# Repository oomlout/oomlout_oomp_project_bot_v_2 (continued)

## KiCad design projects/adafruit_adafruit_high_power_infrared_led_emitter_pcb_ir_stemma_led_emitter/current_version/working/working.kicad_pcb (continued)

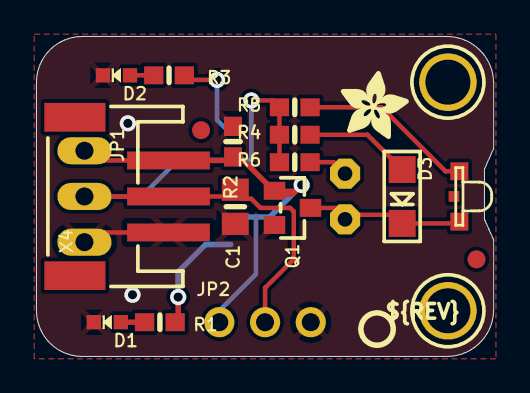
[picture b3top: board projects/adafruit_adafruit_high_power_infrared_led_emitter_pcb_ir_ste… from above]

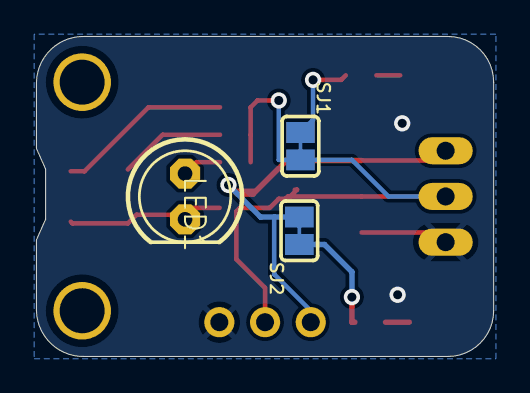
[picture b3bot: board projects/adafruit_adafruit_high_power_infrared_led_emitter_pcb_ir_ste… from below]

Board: 16 copper layers, 25.4 x 17.8 mm, 39 parts (14 on the bottom side), 11 nets.

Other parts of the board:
PLABEL0: PLABEL0
PLABEL00: PLABEL00
PLABEL1: PLABEL1
PLABEL2: PLABEL2
PLABEL3: PLABEL3
PLABEL4: PLABEL4
PLABEL5: PLABEL5
PLABEL6: PLABEL6
PLABEL7: PLABEL7
PLABEL8: PLABEL8
PLABEL9: PLABEL9
PLABEL10: PLABEL10
PLABEL11: PLABEL11
PLABEL13: PLABEL13
PLABEL14: PLABEL14
U$5: PCBFEAT-REV-040
U$10: ADAFRUIT_3.5MM

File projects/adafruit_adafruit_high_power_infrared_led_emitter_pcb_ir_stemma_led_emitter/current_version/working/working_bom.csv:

"Id";"Designator";"Footprint";"Quantity";"Designation";"Supplier and ref";
1;"Q1";"SOT23-WIDE";1;"AO3406";;;
2;"FID3,FID2";"FIDUCIAL_1MM";2;"FIDUCIAL_1MM";;;
3;"PLABEL1";"PLABEL1";1;"";;;
4;"D3";"CHIPLED_1206";1;"1206 IR 940nm";;;
5;"PLABEL2";"PLABEL2";1;"";;;
6;"X4";"JSTPH3";1;"JST PH 3";;;
7;"R6,R4,R5";"0603-NO";3;"22";;;
8;"R1,R2";"0603-NO";2;"10K";;;
9;"D4";"LED_1206_SIDE";1;"1206 IR 940nm Side";;;
10;"PLABEL3";"PLABEL3";1;"";;;
11;"D1";"CHIPLED_0603_NOOUTLINE";1;"RED";;;
12;"C1";"0805-NO";1;"10uF";;;
13;"PLABEL0";"PLABEL0";1;"";;;
14;"U$1,U$8";"MOUNTINGHOLE_2.5_PLATED";2;"MOUNTINGHOLE2.5";;;
15;"U$5";"PCBFEAT-REV-040";1;"";;;
16;"D2";"CHIPLED_0603_NOOUTLINE";1;"GREEN";;;
17;"JP1";"1X03_OVAL";1;"0.1" Header";;;
18;"R3";"0603-NO";1;"33K";;;
19;"JP2";"1X03_ROUND";1;"0.1" Header";;;
20;"U$10";"ADAFRUIT_3.5MM";1;"";;;
21;"PLABEL11";"PLABEL11";1;"";;;
22;"PLABEL13";"PLABEL13";1;"";;;
23;"SJ1,SJ2";"SOLDERJUMPER_CLOSEDWIRE";2;"";;;
24;"PLABEL6";"PLABEL6";1;"";;;
25;"PLABEL9";"PLABEL9";1;"";;;
26;"LED1";"LED5MM";1;"5mm";;;
27;"PLABEL7";"PLABEL7";1;"";;;
28;"PLABEL5";"PLABEL5";1;"";;;
29;"PLABEL4";"PLABEL4";1;"";;;
30;"PLABEL8";"PLABEL8";1;"";;;
31;"PLABEL10";"PLABEL10";1;"";;;
32;"PLABEL14";"PLABEL14";1;"";;;
33;"PLABEL00";"PLABEL00";1;"";;;

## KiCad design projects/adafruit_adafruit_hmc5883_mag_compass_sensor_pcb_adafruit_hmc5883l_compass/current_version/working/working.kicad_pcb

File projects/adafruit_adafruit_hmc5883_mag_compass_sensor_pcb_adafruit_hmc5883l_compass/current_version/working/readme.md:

# adafruit_hmc5883_mag_compass_sensor_pcb
 
## summary 
* id: adafruit_adafruit_hmc5883_mag_compass_sensor_pcb_adafruit_hmc5883l_compass
* user: adafruit
* name: adafruit_hmc5883_mag_compass_sensor_pcb
* board: adafruit_hmc5883l_compass
* repo: https://github.com/adafruit/Adafruit-HMC5883-Mag-Compass-Sensor-PCB

* src_file_repo_sch: 
* src_file_repo_sch_link: https://github.com/adafruit/Adafruit-HMC5883-Mag-Compass-Sensor-PCB/tree/master/
* full details link: https://github.com/oomlout/oomlout_oomp_project_bot_v_2/tree/main/projects/adafruit_adafruit_hmc5883_mag_compass_sensor_pcb_adafruit_hmc5883l_compass/current_version/working  

## schematic  
  
[schematic (pdf)](working_schematic.pdf) 

## pcb  

[board (pdf)](working.pdf)  

## working_bom
| Id | Designator | Footprint | Quantity | Designation | Supplier and ref |  | None | 
| --- | --- | --- | --- | --- | --- | --- | --- | 
| 1 | Q2,Q1 | SOT23-WIDE | 2 | BSS138 |  |  | [''] | 
| 2 | R4,R3 | 0805-NO | 2 | 10K |  |  | [''] | 
| 3 | C3,C5 | C0805 | 2 | 10uF |  |  | [''] | 
| 4 | U2 | SOT23-5 | 1 | MIC5225-3.3V |  |  | [''] | 
| 5 | U$12,U$10,U$11 | FIDUCIAL_1MM | 3 | FIDUCIAL |  |  | [''] | 
| 6 | U$9,U$8 | MOUNTINGHOLE_2.5_PLATED | 2 | MOUNTINGHOLE2.5 |  |  | [''] | 
| 7 | U1 | HMC5883L | 1 | HMC5883L-T |  |  | [''] | 
| 8 | R2,R1 | _0805MP | 2 | 10K |  |  | [''] | 
| 9 | C2 | 0805_10MGAP | 1 | 4.7uF |  |  | [''] | 
| 10 | C4 | C0805 | 1 | 0.22uF |  |  | [''] | 
| 11 | JP1 | 1X06_ROUND_76 | 1 |  |  |  | [''] | 
| 12 | U$7 | ADAFRUIT_5MM | 1 |  |  |  | [''] | 

## bom_schematic
| Ref | Qnty | Value | Cmp name | Footprint | Description | Vendor | DNP | 
| --- | --- | --- | --- | --- | --- | --- | --- | 
| C2 | 1 | 4.7uF | CAP_CERAMIC0805_10MGAP | working:0805_10MGAP |  |  |  | 
| C3, C5 | 2 | 10uF | C-USC0805 | working:C0805 |  |  |  | 
| C4 | 1 | 0.22uF | C-USC0805 | working:C0805 |  |  |  | 
| JP1 | 1 | HEADER-1X676MIL | HEADER-1X676MIL | working:1X06_ROUND_76 |  |  |  | 
| Q1, Q2 | 2 | BSS138 | MOSFET-NWIDE | working:SOT23-WIDE |  |  |  | 
| R1, R2 | 2 | 10K | RESISTOR_0805MP | working:_0805MP |  |  |  | 
| R3, R4 | 2 | 10K | RESISTOR0805_NOOUTLINE | working:0805-NO |  |  |  | 
| U1 | 1 | HMC5883L-T | HMC5883L | working:HMC5883L |  |  |  | 
| U2 | 1 | MIC5225-3.3V | VREG_SOT23-5 | working:SOT23-5 |  |  |  | 
| U$8, U$9 | 2 | MOUNTINGHOLE2.5 | MOUNTINGHOLE2.5 | working:MOUNTINGHOLE_2.5_PLATED |  |  |  | 
| U$10, U$11, U$12 | 3 | FIDUCIAL | FIDUCIAL | working:FIDUCIAL_1MM |  |  |  | 

## mounting_holes
| x | y | package | value | ref | size | 
| --- | --- | --- | --- | --- | --- | 
| 0.0 | 0.0 | MOUNTINGHOLE_2.5_PLATED | MOUNTINGHOLE2.5 | U$8 | m3 | 
| 13.21 | 0.0 | MOUNTINGHOLE_2.5_PLATED | MOUNTINGHOLE2.5 | U$9 | m3 |

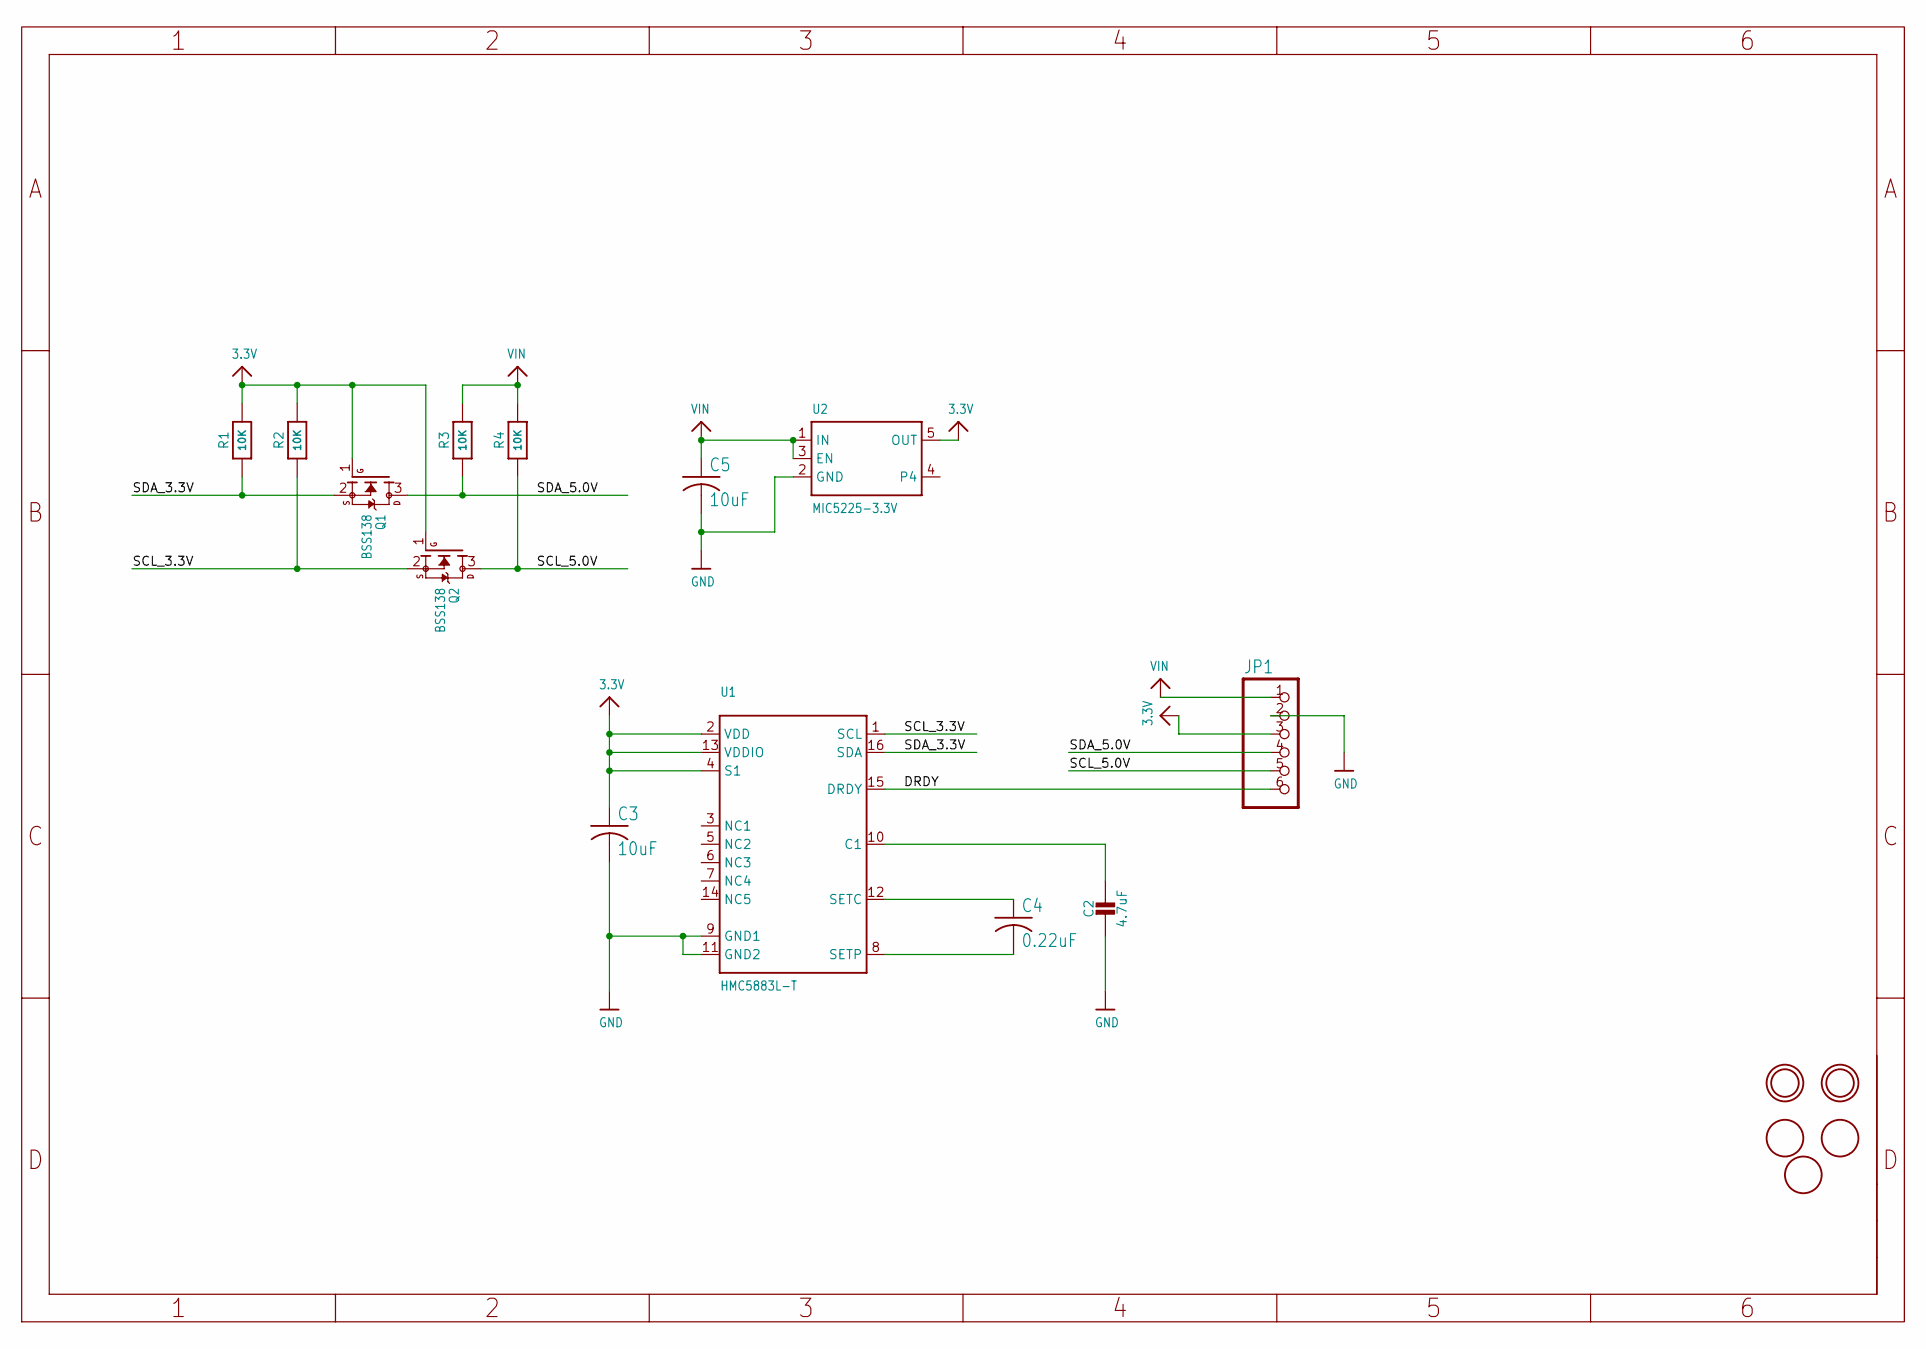
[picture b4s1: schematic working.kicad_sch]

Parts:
C2: 4.7uF; 0805_10MGAP
C3, C5: 10uF; C0805
C4: 0.22uF; C0805
JP1: HEADER-1X676MIL; 1X06_ROUND_76
Q1, Q2: BSS138; SOT23-WIDE
R1, R2: 10K; _0805MP
R3, R4: 10K; 0805-NO
U1: HMC5883L-T; HMC5883L
U2: MIC5225-3.3V; SOT23-5
U$8, U$9: MOUNTINGHOLE2.5; MOUNTINGHOLE_2.5_PLATED
U$10, U$11, U$12: FIDUCIAL; FIDUCIAL_1MM

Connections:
3.3V: C3.1, JP1.3, Q1.1 (G), Q2.1 (G), R1.2, R2.2, U1.2 (VDD), U1.4 (S1), U1.13 (VDDIO), U2.5 (OUT)
DRDY: JP1.6, U1.15 (DRDY)
GND: C2.2, C3.2, C5.2, JP1.2, U1.9 (GND1), U1.11 (GND2), U2.2 (GND)
unnamed: C4.1, U1.12 (SETC)
unnamed: C4.2, U1.8 (SETP)
unnamed: C2.1, U1.10 (C1)
SCL_3.3V: Q2.2 (S), R2.1, U1.1 (SCL)
SCL_5.0V: JP1.5, Q2.3 (D), R4.1
SDA_3.3V: Q1.2 (S), R1.1, U1.16 (SDA)
SDA_5.0V: JP1.4, Q1.3 (D), R3.1
VIN: C5.1, JP1.1, R3.2, R4.2, U2.1 (IN), U2.3 (EN)

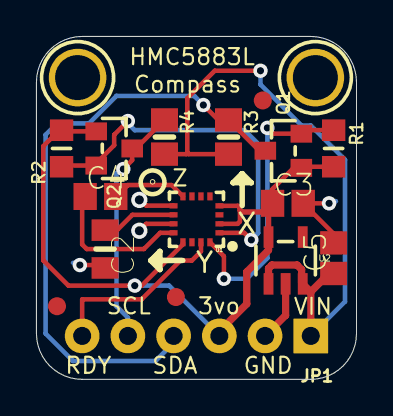
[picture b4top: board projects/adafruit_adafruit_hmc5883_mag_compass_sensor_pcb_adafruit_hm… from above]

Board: 2 copper layers, 17.8 x 19.0 mm, 19 parts (1 on the bottom side), 11 nets.

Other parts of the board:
U$7: ADAFRUIT_5MM

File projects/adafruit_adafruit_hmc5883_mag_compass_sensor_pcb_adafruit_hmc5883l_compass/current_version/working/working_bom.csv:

"Id";"Designator";"Footprint";"Quantity";"Designation";"Supplier and ref";
1;"Q2,Q1";"SOT23-WIDE";2;"BSS138";;;
2;"R4,R3";"0805-NO";2;"10K";;;
3;"C3,C5";"C0805";2;"10uF";;;
4;"U2";"SOT23-5";1;"MIC5225-3.3V";;;
5;"U$12,U$10,U$11";"FIDUCIAL_1MM";3;"FIDUCIAL";;;
6;"U$9,U$8";"MOUNTINGHOLE_2.5_PLATED";2;"MOUNTINGHOLE2.5";;;
7;"U1";"HMC5883L";1;"HMC5883L-T";;;
8;"R2,R1";"_0805MP";2;"10K";;;
9;"C2";"0805_10MGAP";1;"4.7uF";;;
10;"C4";"C0805";1;"0.22uF";;;
11;"JP1";"1X06_ROUND_76";1;"";;;
12;"U$7";"ADAFRUIT_5MM";1;"";;;

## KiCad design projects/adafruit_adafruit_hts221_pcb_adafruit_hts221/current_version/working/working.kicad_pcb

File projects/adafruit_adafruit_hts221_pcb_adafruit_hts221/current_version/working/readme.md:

# adafruit_hts221_pcb
 
## summary 
* id: adafruit_adafruit_hts221_pcb_adafruit_hts221
* user: adafruit
* name: adafruit_hts221_pcb
* board: adafruit_hts221
* repo: https://github.com/adafruit/Adafruit-HTS221-PCB

* src_file_repo_sch: 
* src_file_repo_sch_link: https://github.com/adafruit/Adafruit-HTS221-PCB/tree/master/
* full details link: https://github.com/oomlout/oomlout_oomp_project_bot_v_2/tree/main/projects/adafruit_adafruit_hts221_pcb_adafruit_hts221/current_version/working  

## schematic  
  
[schematic (pdf)](working_schematic.pdf) 

## pcb  

[board (pdf)](working.pdf)  

## working_bom
| Id | Designator | Footprint | Quantity | Designation | Supplier and ref |  | None | 
| --- | --- | --- | --- | --- | --- | --- | --- | 
| 1 | U2 | SOT23-5 | 1 | AP2112K-3.3 |  |  | [''] | 
| 2 | U$17,U$1 | MOUNTINGHOLE_2.5_PLATED | 2 | MOUNTINGHOLE2.5 |  |  | [''] | 
| 3 | @HOLE0,@HOLE1 |  | 2 |  |  |  | [''] | 
| 4 | C1 | 0603-NO | 1 | 0.1uF |  |  | [''] | 
| 5 | JP1 | 1X07_ROUND_70 | 1 |  |  |  | [''] | 
| 6 | CONN4,CONN3 | JST_SH4 | 2 | STEMMA_I2C_QT |  |  | [''] | 
| 7 | R5,R1 | 0603-NO | 2 | 10K |  |  | [''] | 
| 8 | D1 | CHIPLED_0603_NOOUTLINE | 1 | GREEN |  |  | [''] | 
| 9 | FID4,FID3 | FIDUCIAL_1MM | 2 | FIDUCIAL_1MM |  |  | [''] | 
| 10 | X1 | HLGA-6L | 1 | HTS221 |  |  | [''] | 
| 11 | C2,C3 | 0805-NO | 2 | 10uF |  |  | [''] | 
| 12 | D2 | SOD-323 | 1 | 1N4148 |  |  | [''] | 
| 13 | U$4 | ADAFRUIT_3.5MM | 1 |  |  |  | [''] | 
| 14 | R3 | RESPACK_4X0603 | 1 | 10K |  |  | [''] | 
| 15 | Q2 | SOT363 | 1 | BSS138 |  |  | [''] | 
| 16 | U$25 | PCBFEAT-REV-040 | 1 |  |  |  | [''] | 
| 17 | U$30,U$31 | STEMMAQT | 2 |  |  |  | [''] | 

## bom_schematic
| Ref | Qnty | Value | Cmp name | Footprint | Description | Vendor | DNP | 
| --- | --- | --- | --- | --- | --- | --- | --- | 
| C1 | 1 | 0.1uF | CAP_CERAMIC0603_NO | working:0603-NO |  |  |  | 
| C2, C3 | 2 | 10uF | CAP_CERAMIC0805-NOOUTLINE | working:0805-NO |  |  |  | 
| CONN3, CONN4 | 2 | STEMMA_I2C_QT | STEMMA_I2C_QT | working:JST_SH4 |  |  |  | 
| D1 | 1 | GREEN | LED0603_NOOUTLINE | working:CHIPLED_0603_NOOUTLINE |  |  |  | 
| D2 | 1 | 1N4148 | DIODESOD-323 | working:SOD-323 |  |  |  | 
| FID3, FID4 | 2 | FIDUCIAL_1MM | FIDUCIAL_1MM | working:FIDUCIAL_1MM |  |  |  | 
| JP1 | 1 | HEADER-1X770MIL | HEADER-1X770MIL | working:1X07_ROUND_70 |  |  |  | 
| Q2 | 1 | BSS138 | MOSFET-N_DUAL | working:SOT363 |  |  |  | 
| R1, R5 | 2 | 10K | RESISTOR_0603_NOOUT | working:0603-NO |  |  |  | 
| R3 | 1 | 10K | RESISTOR_4PACK | working:RESPACK_4X0603 |  |  |  | 
| U2 | 1 | AP2112K-3.3 | VREG_SOT23-5 | working:SOT23-5 |  |  |  | 
| U$1, U$17 | 2 | MOUNTINGHOLE2.5 | MOUNTINGHOLE2.5 | working:MOUNTINGHOLE_2.5_PLATED |  |  |  | 
| X1 | 1 | HTS221 | HTS221 | working:HLGA-6L |  |  |  | 

## mounting_holes
| x | y | package | value | ref | size | 
| --- | --- | --- | --- | --- | --- | 
| 0.0 | 0.0 | MOUNTINGHOLE_2.5_PLATED | MOUNTINGHOLE2.5 | U$1 | m3 | 
| 20.32 | 0.0 | MOUNTINGHOLE_2.5_PLATED | MOUNTINGHOLE2.5 | U$17 | m3 |

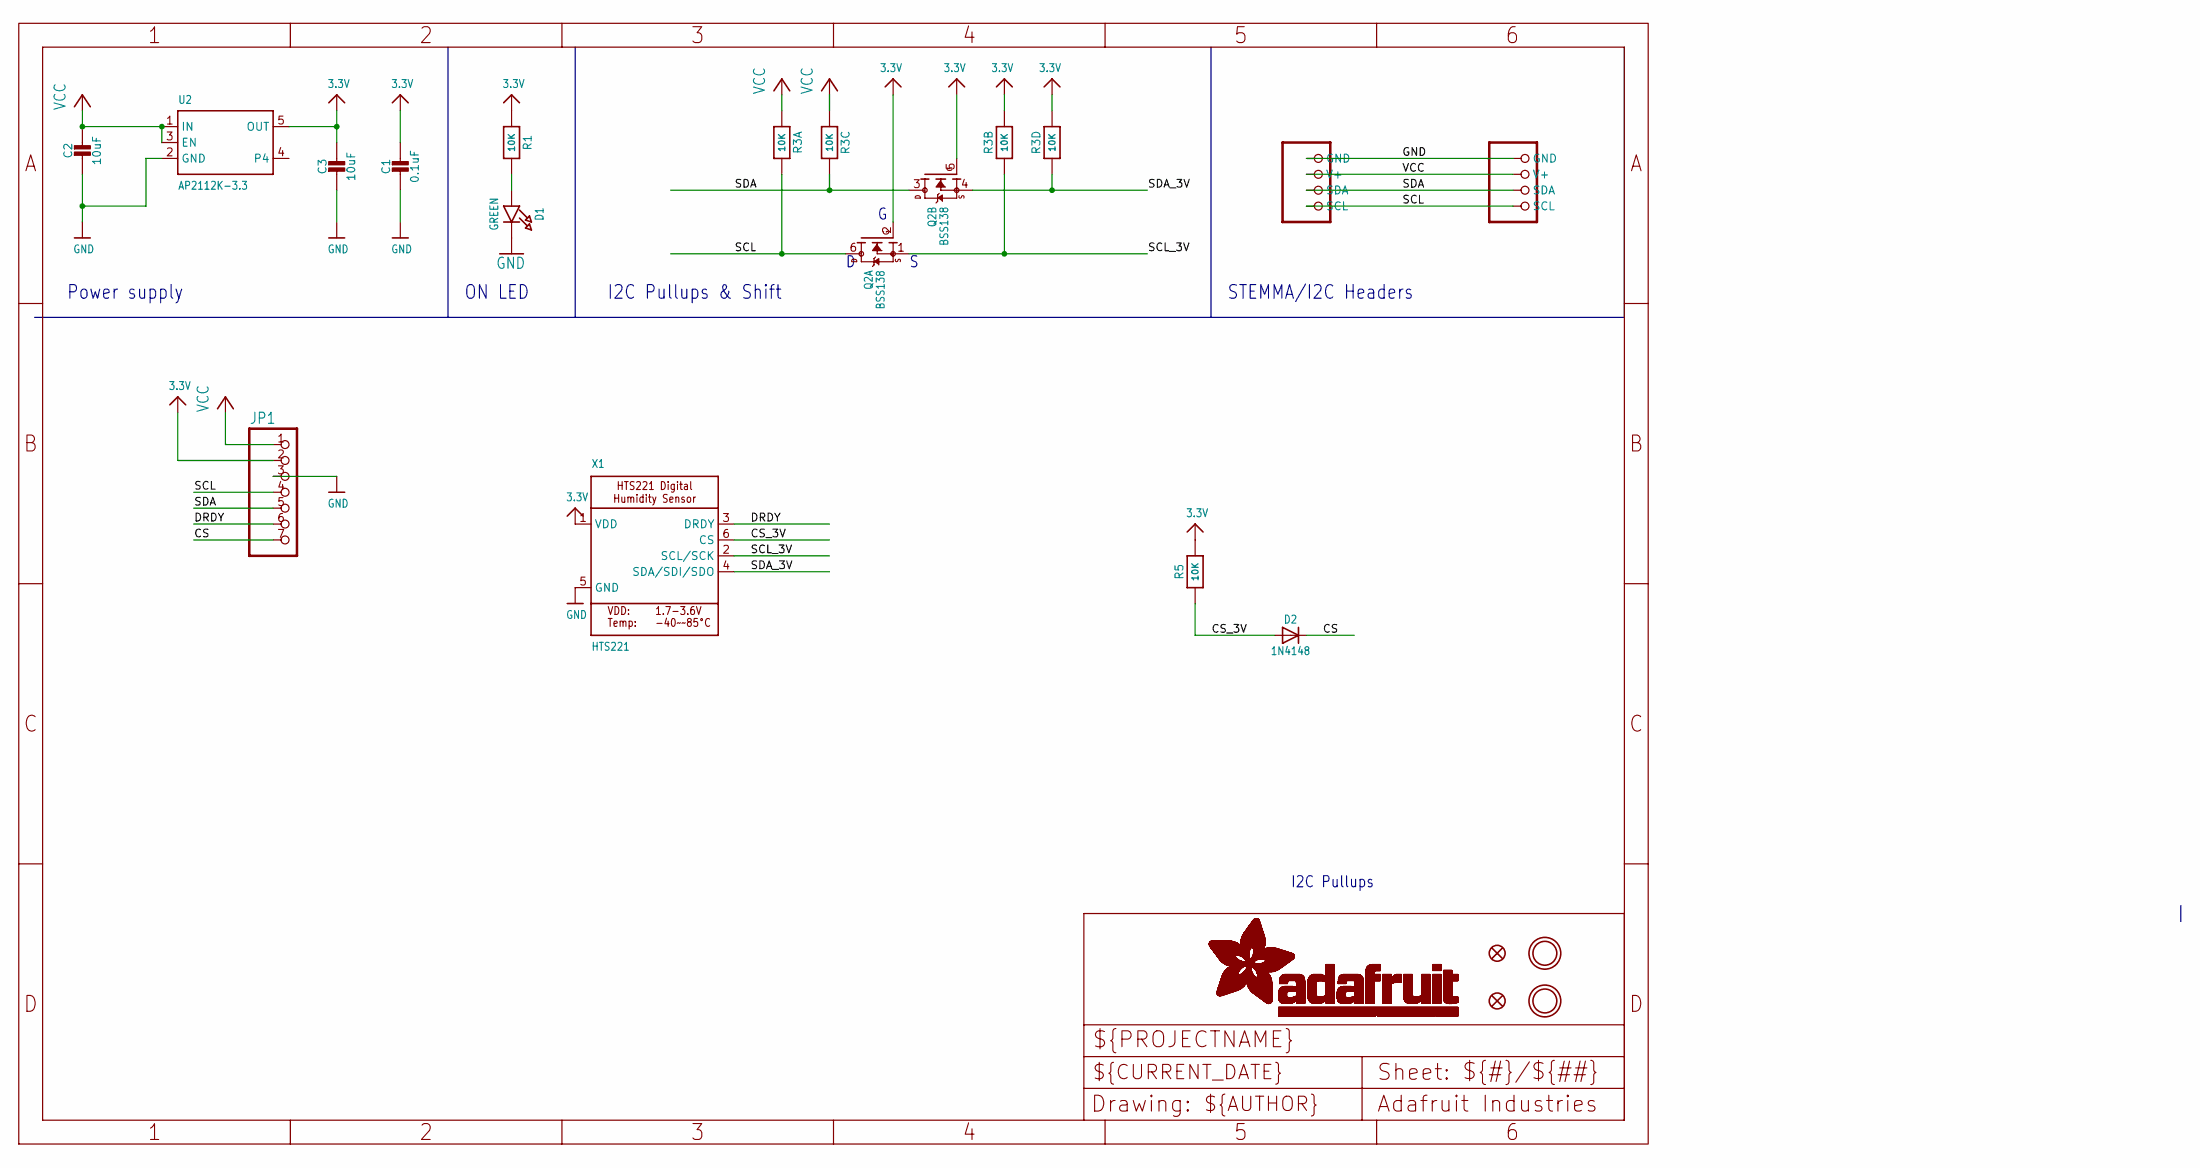
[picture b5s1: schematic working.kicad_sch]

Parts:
C1: 0.1uF; 0603-NO
C2, C3: 10uF; 0805-NO
CONN3, CONN4: STEMMA_I2C_QT; JST_SH4
D1: GREEN; CHIPLED_0603_NOOUTLINE
D2: 1N4148; SOD-323
FID3, FID4: FIDUCIAL_1MM
JP1: HEADER-1X770MIL; 1X07_ROUND_70
Q2: BSS138; SOT363
R1, R5: 10K; 0603-NO
R3: 10K; RESPACK_4X0603
U2: AP2112K-3.3; SOT23-5
U$1, U$17: MOUNTINGHOLE2.5; MOUNTINGHOLE_2.5_PLATED
X1: HTS221; HLGA-6L

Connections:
3.3V: C1.1, C3.1, JP1.2, Q2.2 (G), Q2.5 (G), R1.1, R3.2 (1), R3.4 (1), R5.2, U2.5 (OUT), X1.1 (VDD)
CS: D2.C, JP1.7
CS_3V: D2.A, R5.1, X1.6 (CS)
DRDY: JP1.6, X1.3 (DRDY)
GND: C1.2, C2.2, C3.2, CONN3.1 (GND), CONN4.1 (GND), D1.C, JP1.3, U2.2 (GND), X1.5 (GND)
unnamed: D1.A, R1.2
SCL: CONN3.4 (SCL), CONN4.4 (SCL), JP1.4, Q2.6 (D), R3.8 (2)
SCL_3V: Q2.1 (S), R3.7 (2), X1.2 (SCL/SCK)
SDA: CONN3.3 (SDA), CONN4.3 (SDA), JP1.5, Q2.3 (D), R3.6 (2)
SDA_3V: Q2.4 (S), R3.5 (2), X1.4 (SDA/SDI/SDO)
VCC: C2.1, CONN3.2 (V+), CONN4.2 (V+), JP1.1, R3.1, R3.3 (1), U2.1 (IN), U2.3 (EN)

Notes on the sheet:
STEMMA/I2C Headers
Power supply
ON LED
I2C Pullups
I2C Pullups & Shift

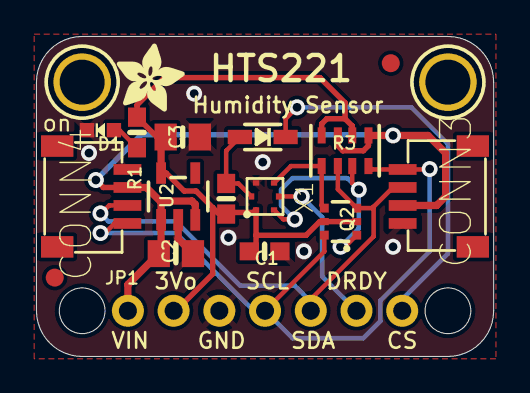
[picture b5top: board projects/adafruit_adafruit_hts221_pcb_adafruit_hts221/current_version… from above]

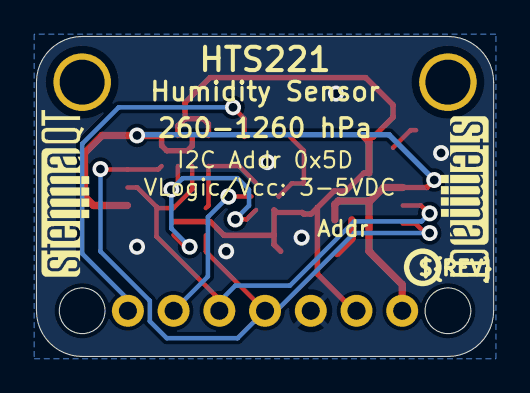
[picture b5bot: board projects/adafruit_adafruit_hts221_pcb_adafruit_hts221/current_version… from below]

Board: 2 copper layers, 25.4 x 17.8 mm, 24 parts (3 on the bottom side), 11 nets.

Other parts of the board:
@HOLE0, @HOLE1: (no value)
U$4: ADAFRUIT_3.5MM
U$25: PCBFEAT-REV-040
U$30, U$31: STEMMAQT

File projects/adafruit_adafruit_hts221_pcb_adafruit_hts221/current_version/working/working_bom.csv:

"Id";"Designator";"Footprint";"Quantity";"Designation";"Supplier and ref";
1;"U2";"SOT23-5";1;"AP2112K-3.3";;;
2;"U$17,U$1";"MOUNTINGHOLE_2.5_PLATED";2;"MOUNTINGHOLE2.5";;;
3;"@HOLE0,@HOLE1";"";2;"";;;
4;"C1";"0603-NO";1;"0.1uF";;;
5;"JP1";"1X07_ROUND_70";1;"";;;
6;"CONN4,CONN3";"JST_SH4";2;"STEMMA_I2C_QT";;;
7;"R5,R1";"0603-NO";2;"10K";;;
8;"D1";"CHIPLED_0603_NOOUTLINE";1;"GREEN";;;
9;"FID4,FID3";"FIDUCIAL_1MM";2;"FIDUCIAL_1MM";;;
10;"X1";"HLGA-6L";1;"HTS221";;;
11;"C2,C3";"0805-NO";2;"10uF";;;
12;"D2";"SOD-323";1;"1N4148";;;
13;"U$4";"ADAFRUIT_3.5MM";1;"";;;
14;"R3";"RESPACK_4X0603";1;"10K";;;
15;"Q2";"SOT363";1;"BSS138";;;
16;"U$25";"PCBFEAT-REV-040";1;"";;;
17;"U$30,U$31";"STEMMAQT";2;"";;;

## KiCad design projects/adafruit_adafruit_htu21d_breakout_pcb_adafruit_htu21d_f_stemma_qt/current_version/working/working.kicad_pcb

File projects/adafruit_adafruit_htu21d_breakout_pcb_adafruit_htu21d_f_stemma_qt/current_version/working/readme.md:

# adafruit_htu21d_breakout_pcb
 
## summary 
* id: adafruit_adafruit_htu21d_breakout_pcb_adafruit_htu21d_f_stemma_qt
* user: adafruit
* name: adafruit_htu21d_breakout_pcb
* board: adafruit_htu21d_f_stemma_qt
* repo: https://github.com/adafruit/Adafruit-HTU21D-Breakout-PCB

* src_file_repo_sch: 
* src_file_repo_sch_link: https://github.com/adafruit/Adafruit-HTU21D-Breakout-PCB/tree/master/
* full details link: https://github.com/oomlout/oomlout_oomp_project_bot_v_2/tree/main/projects/adafruit_adafruit_htu21d_breakout_pcb_adafruit_htu21d_f_stemma_qt/current_version/working  

## schematic  
  
[schematic (pdf)](working_schematic.pdf) 

## pcb  

[board (pdf)](working.pdf)  

## working_bom
| Id | Designator | Footprint | Quantity | Designation | Supplier and ref |  | None | 
| --- | --- | --- | --- | --- | --- | --- | --- | 
| 1 | Q3 | SOT363 | 1 | BSS138 |  |  | [''] | 
| 2 | CONN3,CONN4 | JST_SH4 | 2 | STEMMA_I2C_QT |  |  | [''] | 
| 3 | FID4,FID3 | FIDUCIAL_1MM | 2 | FIDUCIAL_1MM |  |  | [''] | 
| 4 | C5,C4 | 0805-NO | 2 | 10uF |  |  | [''] | 
| 5 | JP1 | 1X05_ROUND_70 | 1 |  |  |  | [''] | 
| 6 | U$25,U$22,U$19,U$20 | MOUNTINGHOLE_2.5_PLATED | 4 | MOUNTINGHOLE2.5 |  |  | [''] | 
| 7 | C6 | 0603-NO | 1 | 0.1uF |  |  | [''] | 
| 8 | U1 | HTU21DF | 1 | HTU21D-F |  |  | [''] | 
| 9 | U3 | SOT23-5 | 1 | AP2112K-3.3 |  |  | [''] | 
| 10 | D1 | CHIPLED_0603_NOOUTLINE | 1 | GREEN |  |  | [''] | 
| 11 | U$28 | ADAFRUIT_3.5MM | 1 |  |  |  | [''] | 
| 12 | R5 | RESPACK_4X0603 | 1 | 10K |  |  | [''] | 
| 13 | R6 | 0603-NO | 1 | 10K |  |  | [''] | 
| 14 | U$30,U$31 | STEMMAQT | 2 |  |  |  | [''] | 
| 15 | U$29 | PCBFEAT-REV-040 | 1 |  |  |  | [''] | 

## bom_schematic
| Ref | Qnty | Value | Cmp name | Footprint | Description | Vendor | DNP | 
| --- | --- | --- | --- | --- | --- | --- | --- | 
| C4, C5 | 2 | 10uF | CAP_CERAMIC0805-NOOUTLINE | working:0805-NO |  |  |  | 
| C6 | 1 | 0.1uF | CAP_CERAMIC0603_NO | working:0603-NO |  |  |  | 
| CONN3, CONN4 | 2 | STEMMA_I2C_QT | STEMMA_I2C_QT | working:JST_SH4 |  |  |  | 
| D1 | 1 | GREEN | LED0603_NOOUTLINE | working:CHIPLED_0603_NOOUTLINE |  |  |  | 
| FID3, FID4 | 2 | FIDUCIAL_1MM | FIDUCIAL_1MM | working:FIDUCIAL_1MM |  |  |  | 
| JP1 | 1 | HEADER-1X570MIL | HEADER-1X570MIL | working:1X05_ROUND_70 |  |  |  | 
| Q3 | 1 | BSS138 | MOSFET-N_DUAL | working:SOT363 |  |  |  | 
| R5 | 1 | 10K | RESISTOR_4PACK | working:RESPACK_4X0603 |  |  |  | 
| R6 | 1 | 10K | RESISTOR_0603_NOOUT | working:0603-NO |  |  |  | 
| U1 | 1 | HTU21D-F | HTU21DF | working:HTU21DF |  |  |  | 
| U3 | 1 | AP2112K-3.3 | VREG_SOT23-5 | working:SOT23-5 |  |  |  | 
| U$19, U$20, U$22, U$25 | 4 | MOUNTINGHOLE2.5 | MOUNTINGHOLE2.5 | working:MOUNTINGHOLE_2.5_PLATED |  |  |  | 

## mounting_holes
| x | y | package | value | ref | size | 
| --- | --- | --- | --- | --- | --- | 
| 0.0 | 12.7 | MOUNTINGHOLE_2.5_PLATED | MOUNTINGHOLE2.5 | U$19 | m3 | 
| 20.32 | 12.7 | MOUNTINGHOLE_2.5_PLATED | MOUNTINGHOLE2.5 | U$20 | m3 | 
| 0.0 | 0.0 | MOUNTINGHOLE_2.5_PLATED | MOUNTINGHOLE2.5 | U$22 | m3 | 
| 20.32 | 0.0 | MOUNTINGHOLE_2.5_PLATED | MOUNTINGHOLE2.5 | U$25 | m3 |

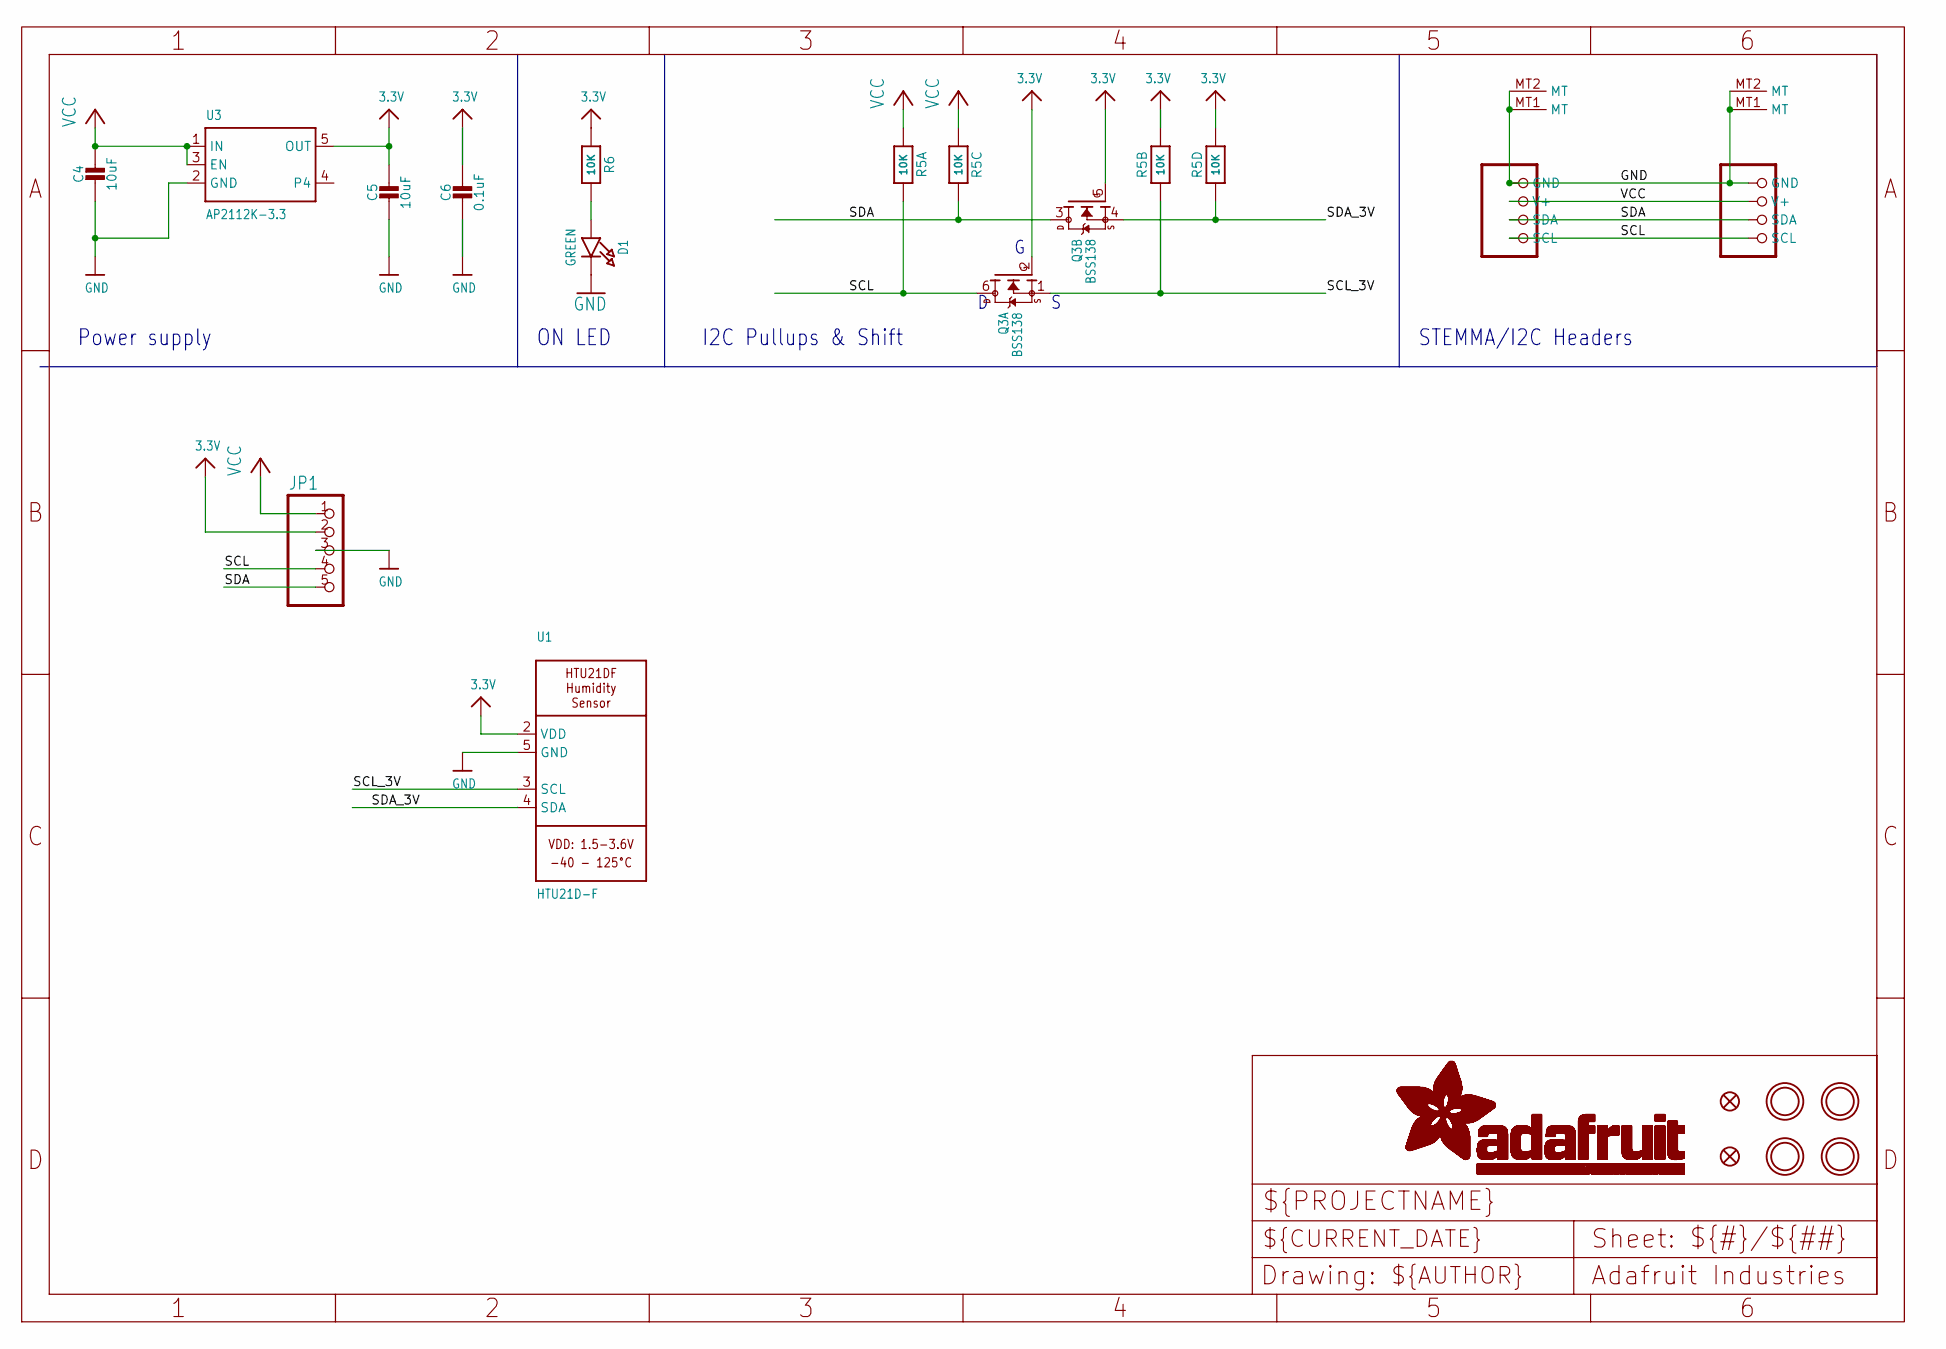
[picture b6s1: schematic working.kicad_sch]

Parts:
C4, C5: 10uF; 0805-NO
C6: 0.1uF; 0603-NO
CONN3, CONN4: STEMMA_I2C_QT; JST_SH4
D1: GREEN; CHIPLED_0603_NOOUTLINE
FID3, FID4: FIDUCIAL_1MM
JP1: HEADER-1X570MIL; 1X05_ROUND_70
Q3: BSS138; SOT363
R5: 10K; RESPACK_4X0603
R6: 10K; 0603-NO
U1: HTU21D-F; HTU21DF
U3: AP2112K-3.3; SOT23-5
U$19, U$20, U$22, U$25: MOUNTINGHOLE2.5; MOUNTINGHOLE_2.5_PLATED

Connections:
3.3V: C5.1, C6.1, JP1.2, Q3.2 (G), Q3.5 (G), R5.2 (1), R5.4 (1), R6.1, U1.2 (VDD), U3.5 (OUT)
GND: C4.2, C5.2, C6.2, CONN3.1 (GND), CONN3.MT1 (MT), CONN3.MT2 (MT), CONN4.1 (GND), CONN4.MT1 (MT), CONN4.MT2 (MT), D1.C, JP1.3, U1.5 (GND), U3.2 (GND)
unnamed: D1.A, R6.2
SCL: CONN3.4 (SCL), CONN4.4 (SCL), JP1.4, Q3.6 (D), R5.8 (2)
SCL_3V: Q3.1 (S), R5.7 (2), U1.3 (SCL)
SDA: CONN3.3 (SDA), CONN4.3 (SDA), JP1.5, Q3.3 (D), R5.6 (2)
SDA_3V: Q3.4 (S), R5.5 (2), U1.4 (SDA)
VCC: C4.1, CONN3.2 (V+), CONN4.2 (V+), JP1.1, R5.1, R5.3 (1), U3.1 (IN), U3.3 (EN)

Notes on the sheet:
STEMMA/I2C Headers
I2C Pullups & Shift
ON LED
Power supply

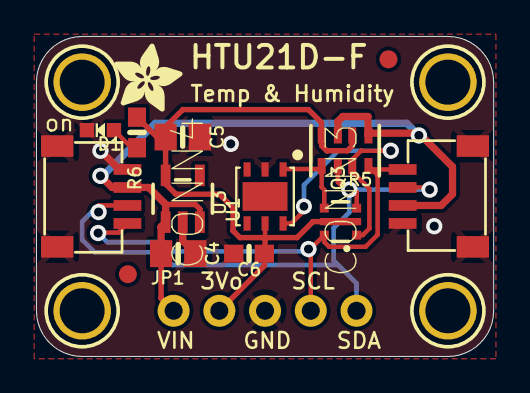
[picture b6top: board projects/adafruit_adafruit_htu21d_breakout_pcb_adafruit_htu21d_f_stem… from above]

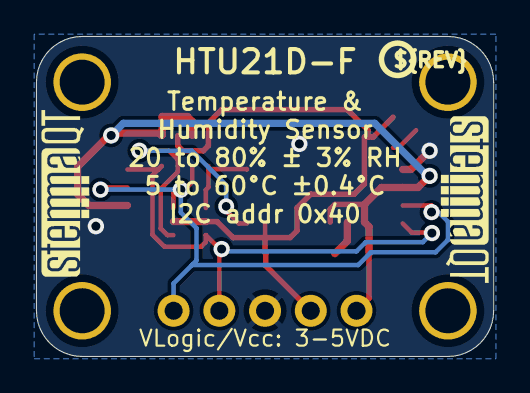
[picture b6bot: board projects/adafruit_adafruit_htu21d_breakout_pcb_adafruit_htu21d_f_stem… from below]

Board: 2 copper layers, 25.4 x 17.8 mm, 22 parts (3 on the bottom side), 8 nets.

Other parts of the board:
U$28: ADAFRUIT_3.5MM
U$29: PCBFEAT-REV-040
U$30, U$31: STEMMAQT

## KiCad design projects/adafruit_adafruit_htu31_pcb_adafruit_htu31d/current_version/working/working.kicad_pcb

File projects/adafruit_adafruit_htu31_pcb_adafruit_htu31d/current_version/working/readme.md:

# adafruit_htu31_pcb
 
## summary 
* id: adafruit_adafruit_htu31_pcb_adafruit_htu31d
* user: adafruit
* name: adafruit_htu31_pcb
* board: adafruit_htu31d
* repo: https://github.com/adafruit/Adafruit-HTU31-PCB

* src_file_repo_sch: 
* src_file_repo_sch_link: https://github.com/adafruit/Adafruit-HTU31-PCB/tree/main/
* full details link: https://github.com/oomlout/oomlout_oomp_project_bot_v_2/tree/main/projects/adafruit_adafruit_htu31_pcb_adafruit_htu31d/current_version/working  

## schematic  
  
[schematic (pdf)](working_schematic.pdf) 

## pcb  

[board (pdf)](working.pdf)  

## working_bom
| Id | Designator | Footprint | Quantity | Designation | Supplier and ref |  | None | 
| --- | --- | --- | --- | --- | --- | --- | --- | 
| 1 | CONN3,CONN4 | JST_SH4 | 2 | STEMMA_I2C_QT |  |  | [''] | 
| 2 | U$28 | ADAFRUIT_3.5MM | 1 |  |  |  | [''] | 
| 3 | U$25,U$20,U$19,U$22 | MOUNTINGHOLE_2.5_PLATED | 4 | MOUNTINGHOLE2.5 |  |  | [''] | 
| 4 | C6 | 0603-NO | 1 | 0.1uF |  |  | [''] | 
| 5 | C5 | 0805-NO | 1 | 10uF |  |  | [''] | 
| 6 | D1 | CHIPLED_0603_NOOUTLINE | 1 | GREEN |  |  | [''] | 
| 7 | R1 | 0603-NO | 1 | 220 |  |  | [''] | 
| 8 | FID4,FID3 | FIDUCIAL_1MM | 2 | FIDUCIAL_1MM |  |  | [''] | 
| 9 | JP1 | 1X06_ROUND_70 | 1 |  |  |  | [''] | 
| 10 | R5 | RESPACK_4X0603 | 1 | 10K |  |  | [''] | 
| 11 | R2 | 0603-NO | 1 | 10K |  |  | [''] | 
| 12 | X1 | HTU31D | 1 | HTU31D_ |  |  | [''] | 
| 13 | SJ1 | SOLDERJUMPER_ARROW_NOPASTE | 1 |  |  |  | [''] | 
| 14 | U$31,U$30 | STEMMAQT | 2 |  |  |  | [''] | 
| 15 | U$29 | PCBFEAT-REV-040 | 1 |  |  |  | [''] | 

## bom_schematic
| Ref | Qnty | Value | Cmp name | Footprint | Description | Vendor | DNP | 
| --- | --- | --- | --- | --- | --- | --- | --- | 
| C5 | 1 | 10uF | CAP_CERAMIC0805-NOOUTLINE | working:0805-NO |  |  |  | 
| C6 | 1 | 0.1uF | CAP_CERAMIC0603_NO | working:0603-NO |  |  |  | 
| CONN3, CONN4 | 2 | STEMMA_I2C_QT | STEMMA_I2C_QT | working:JST_SH4 |  |  |  | 
| D1 | 1 | GREEN | LED0603_NOOUTLINE | working:CHIPLED_0603_NOOUTLINE |  |  |  | 
| FID3, FID4 | 2 | FIDUCIAL_1MM | FIDUCIAL_1MM | working:FIDUCIAL_1MM |  |  |  | 
| JP1 | 1 | HEADER-1X670MIL | HEADER-1X670MIL | working:1X06_ROUND_70 |  |  |  | 
| R1 | 1 | 220 | RESISTOR_0603_NOOUT | working:0603-NO |  |  |  | 
| R2 | 1 | 10K | RESISTOR_0603_NOOUT | working:0603-NO |  |  |  | 
| R5 | 1 | 10K | RESISTOR_4PACK | working:RESPACK_4X0603 |  |  |  | 
| SJ1 | 1 | SOLDERJUMPER | SOLDERJUMPER | working:SOLDERJUMPER_ARROW_NOPASTE |  |  |  | 
| U$19, U$20, U$22, U$25 | 4 | MOUNTINGHOLE2.5 | MOUNTINGHOLE2.5 | working:MOUNTINGHOLE_2.5_PLATED |  |  |  | 
| X1 | 1 | HTU31D_ | HTU31D_ | working:HTU31D |  |  |  | 

## mounting_holes
| x | y | package | value | ref | size | 
| --- | --- | --- | --- | --- | --- | 
| 0.0 | 12.7 | MOUNTINGHOLE_2.5_PLATED | MOUNTINGHOLE2.5 | U$19 | m3 | 
| 20.32 | 12.7 | MOUNTINGHOLE_2.5_PLATED | MOUNTINGHOLE2.5 | U$20 | m3 | 
| 0.0 | 0.0 | MOUNTINGHOLE_2.5_PLATED | MOUNTINGHOLE2.5 | U$22 | m3 | 
| 20.32 | 0.0 | MOUNTINGHOLE_2.5_PLATED | MOUNTINGHOLE2.5 | U$25 | m3 |

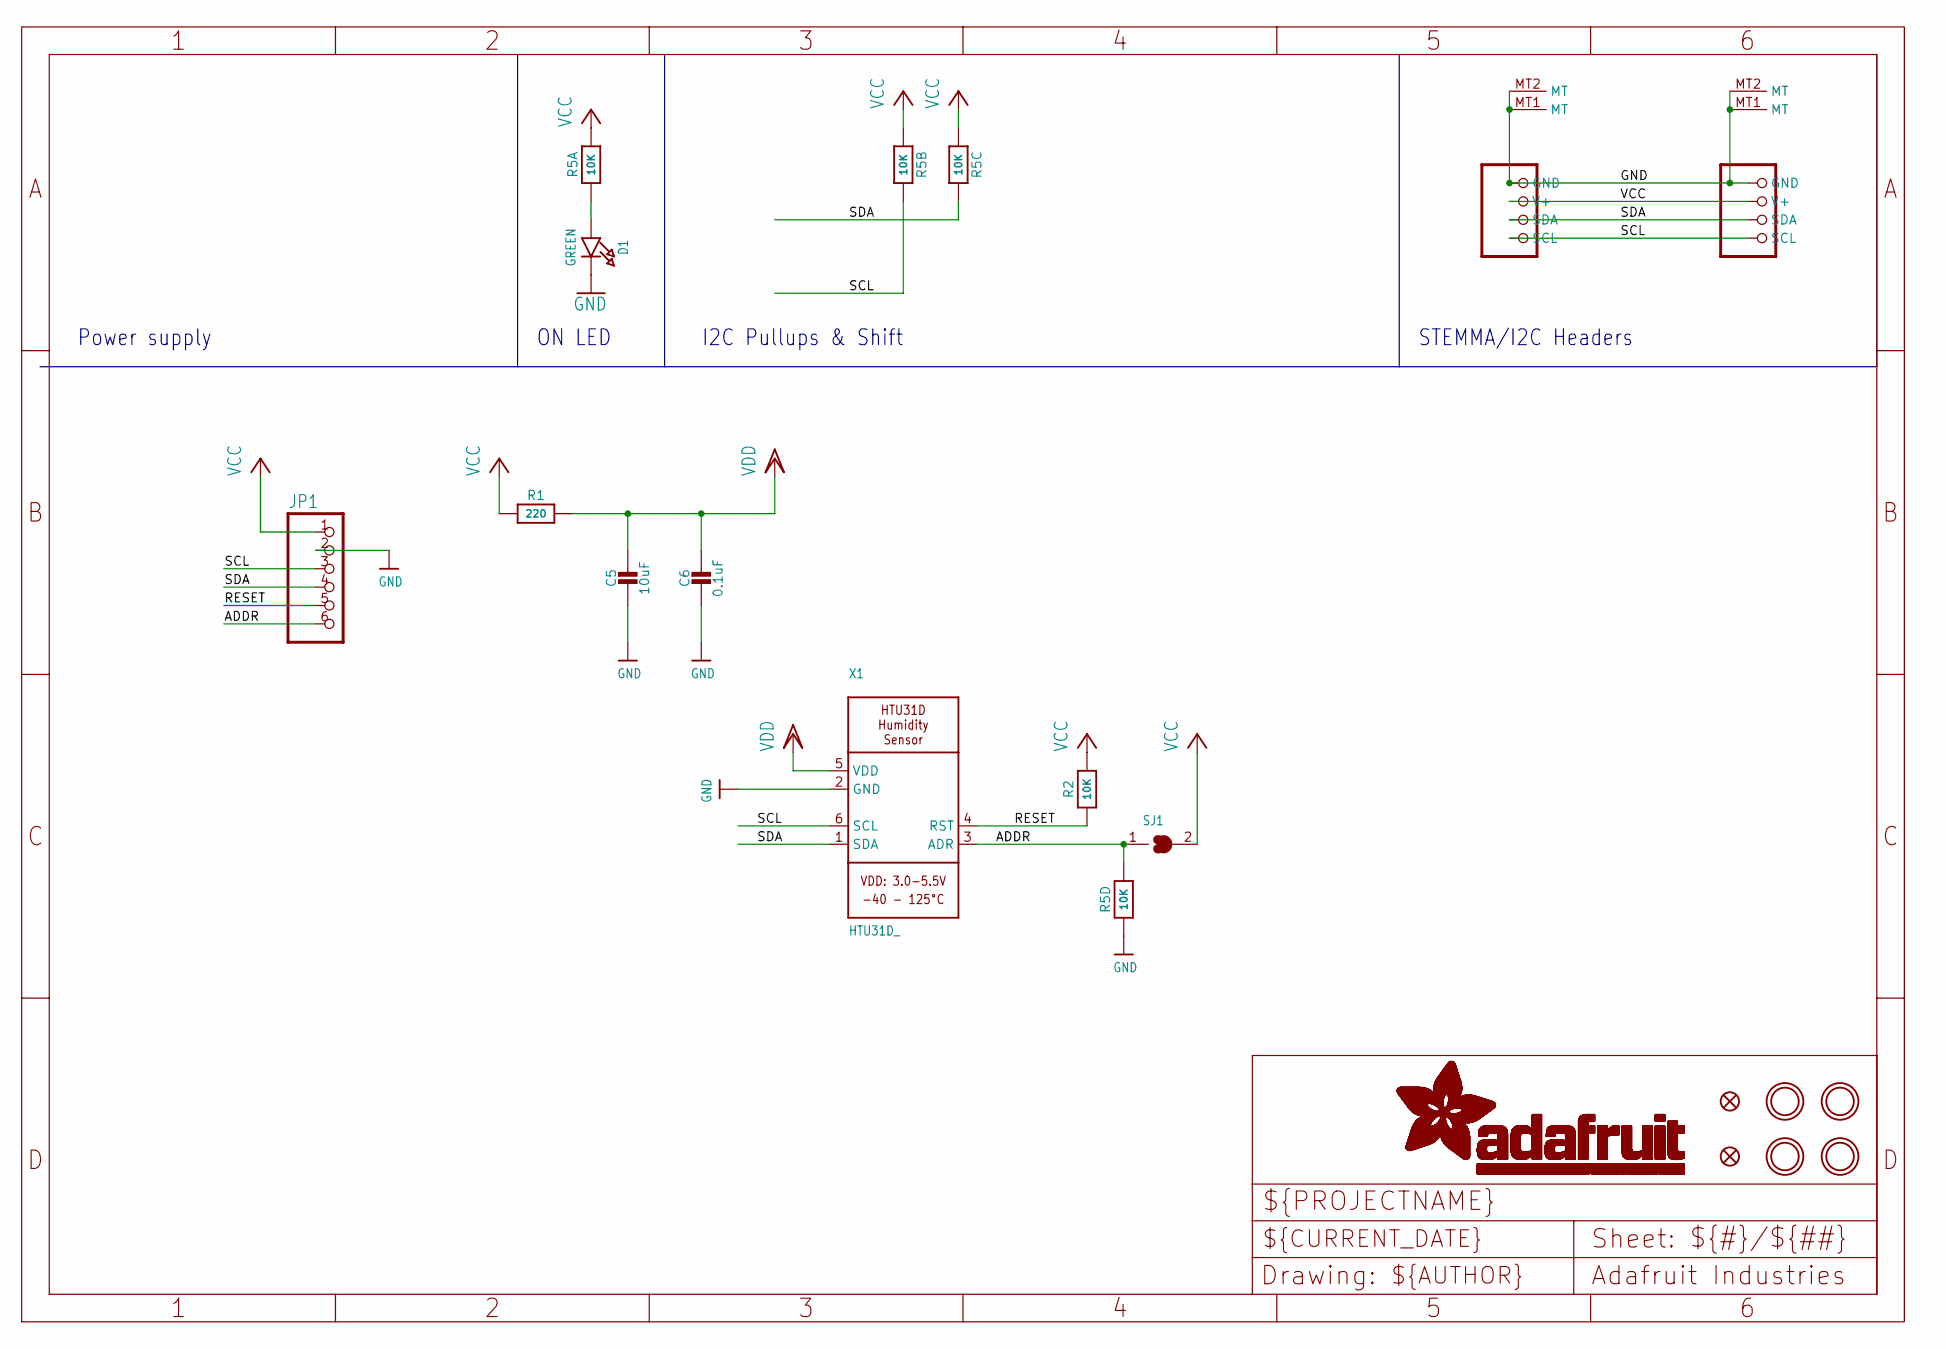
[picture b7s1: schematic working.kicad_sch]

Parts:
C5: 10uF; 0805-NO
C6: 0.1uF; 0603-NO
CONN3, CONN4: STEMMA_I2C_QT; JST_SH4
D1: GREEN; CHIPLED_0603_NOOUTLINE
FID3, FID4: FIDUCIAL_1MM
JP1: HEADER-1X670MIL; 1X06_ROUND_70
R1: 220; 0603-NO
R2: 10K; 0603-NO
R5: 10K; RESPACK_4X0603
SJ1: SOLDERJUMPER; SOLDERJUMPER_ARROW_NOPASTE
U$19, U$20, U$22, U$25: MOUNTINGHOLE2.5; MOUNTINGHOLE_2.5_PLATED
X1: HTU31D_; HTU31D

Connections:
ADDR: JP1.6, R5.5 (2), SJ1.1, X1.3 (ADR)
GND: C5.2, C6.2, CONN3.1 (GND), CONN3.MT1 (MT), CONN3.MT2 (MT), CONN4.1 (GND), CONN4.MT1 (MT), CONN4.MT2 (MT), D1.C, JP1.2, R5.4 (1), X1.2 (GND)
unnamed: D1.A, R5.1
RESET: JP1.5, R2.1, X1.4 (RST)
SCL: CONN3.4 (SCL), CONN4.4 (SCL), JP1.3, R5.7 (2), X1.6 (SCL)
SDA: CONN3.3 (SDA), CONN4.3 (SDA), JP1.4, R5.6 (2), X1.1 (SDA)
VCC: CONN3.2 (V+), CONN4.2 (V+), JP1.1, R1.1, R2.2, R5.2 (1), R5.3 (1), R5.8 (2), SJ1.2
VDD: C5.1, C6.1, R1.2, X1.5 (VDD)

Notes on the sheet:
Power supply
ON LED
I2C Pullups & Shift
STEMMA/I2C Headers

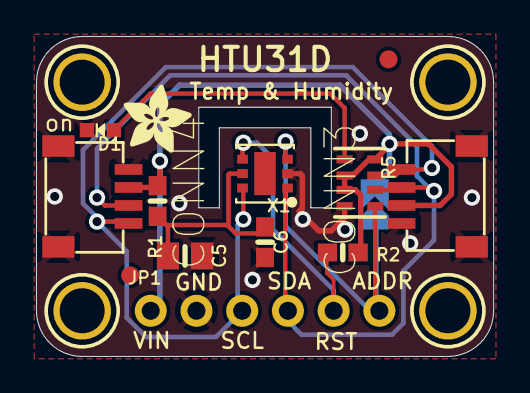
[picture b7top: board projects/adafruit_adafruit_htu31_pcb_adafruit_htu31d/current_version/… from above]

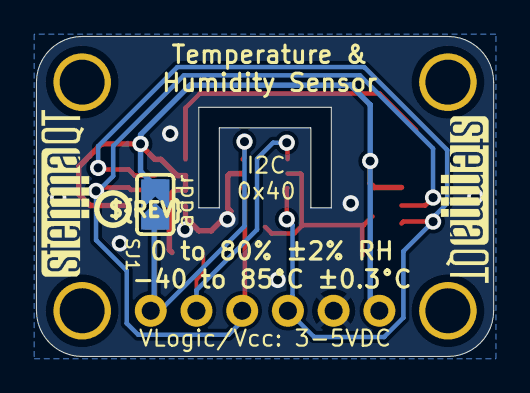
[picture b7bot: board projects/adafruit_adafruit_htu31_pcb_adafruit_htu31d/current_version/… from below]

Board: 2 copper layers, 25.4 x 17.8 mm, 21 parts (4 on the bottom side), 8 nets.

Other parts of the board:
U$28: ADAFRUIT_3.5MM
U$29: PCBFEAT-REV-040
U$30, U$31: STEMMAQT
